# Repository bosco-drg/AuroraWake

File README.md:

# AuroraWake

> A smart alarm clock that gently guides you into waking up instead of startling you.

AuroraWake is a light and sound alarm clock project designed to make waking up feel more natural. The device gradually adjusts its light intensity and, if necessary, adds a gentle sound at the selected time.

## Goals

- Reduce sudden and unpleasant wake-ups.
- Use gradually increasing light as the primary wake-up signal.
- Keep the experience simple, quiet, and respectful of sleep.
- Design an accessible, repairable, and well-documented device.

## Project structure

```text
AuroraWake/
├── docs/        Documentation, schematics, and design decisions
├── hardware/    Schematics, PCB, and manufacturing files
└── README.md    Project overview
```

## Development status

The project is currently in the electronic design phase. The overall architecture is built around an **ESP32** controller, which will coordinate:

- gradual lighting through a voltage dimmer;
- alarm information on the display;
- the speaker through an audio amplifier;
- the physical buttons and the RTC clock;
- Bluetooth communication with a smartphone application.

The next step is to select suitable components and check their compatibility. The schematic will then be refined before the first prototype is designed.

<div align="center">
	
</div>

<p align="center"><em>Preliminary functional architecture of AuroraWake.</em></p>

## Author

Project designed and developed by **Bosco drg**.

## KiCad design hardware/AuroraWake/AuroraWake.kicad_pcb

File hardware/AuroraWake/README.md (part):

# AuroraWake V2 — Carte réveil ESP32-S3 (12 V)

Projet KiCad 9, **schéma complet sur une seule feuille A1** (8 blocs fonctionnels encadrés), généré depuis [tools/design.py](tools/design.py).
ERC : **0 erreur, 1 avertissement accepté** (pad thermique du MAX98357A, de type « unspecified », relié à GND).
Le schéma est exporté en PDF dans [docs/AuroraWake_schema.pdf](docs/AuroraWake_schema.pdf) et la BOM brute KiCad dans [docs/bom_kicad.csv](docs/bom_kicad.csv).

## 0. Décisions et hypothèses

| Sujet | Décision | Pourquoi |
|---|---|---|
| Entrée | Jack DC conservé : **CUI PJ-063AH, 8 A** | Un jack ne supporte pas 17 A, donc le **panneau est limité à 50 W (4,2 A)**. Courant total ≈ 4,9 A, soit environ 60 % du calibre du jack. |
| Panneau 60 W | Possible, avec un fusible NANO² **10 A** | 5,7 A au total : le fusible de 7 A fonctionnerait alors à 81 % de son calibre, au-delà de la règle des 75 %. La marge sur le jack se réduit. |
| Bloc d'alimentation | **12 V ≥ 6 A** (≥ 8 A pour un panneau de 60 W) | — |
| Module | **ESP32-S3-WROOM-1-N16R8** (module nu) | 16 Mo de flash pour les sons, 8 Mo de PSRAM pour les tampons audio. Un DevKitC-1 N16R8 suffit pour développer le firmware en attendant les cartes. |
| Fabrication | JLCPCB PCBA, **2 couches, cuivre 2 oz**, environ 100 × 80 mm | Les pièces traversantes (jack, bornier, boutons, buzzer, barrettes) sont soudées à la main ou en option THT. |
| Références LCSC | **Non renseignées** | À compléter au moment du rapprochement de la BOM chez JLCPCB. Chaque MPN est dans le champ `MPN` du symbole. |

## 1. BOM (justifiée)

Liste complète et regroupée : [docs/bom_kicad.csv](docs/bom_kicad.csv), soit 112 composants. Les composants structurants :

| Réf | Composant | Boîtier | Justification / alternative |
|---|---|---|---|
| J101 | Jack DC CUI PJ-063AH | THT | Jack 8 A. Broche centrale de 2,0 mm : **vérifier la fiche du bloc d'alimentation** (5,5×2,1). |
| F101 | Fusible Littelfuse NANO² 451, **7 A rapide** (0451007.MRL) | CMS 7,5 × 3,8 mm | 10 fois plus petit que le 5×20, assemblé par JLCPCB. Charge de 70 % à 4,9 A. L'appel de courant de C101 au branchement (≈0,3 A²s) reste très inférieur à l'I²t du fusible : à vérifier dans la datasheet. Soudé, donc non remplaçable ; pour un fusible remplaçable, utiliser le porte-fusible OMNI-BLOK 157x, de même encombrement. |
| Q101 | AOD4185 (P-MOS −40 V, ≈15 mΩ) | TO-252 | Protection contre l'inversion de polarité : 0,36 W de pertes contre ≈2,5 W pour une Schottky. Alternative : contrôleur de diode idéale LM74700 avec un N-MOS. |
| D101 | BZT52C15 | SOD-123 | Limite Vgs de Q101 à 15 V (maximum autorisé : ±20 V). |
| D102 | SMBJ15A (TVS 600 W) | SMB | Écrête les surtensions à ~24 V. Placée **après** Q101 pour ne pas être sollicitée en cas d'inversion. |
| C101 / C102 | 470 µF 35 V électrolytique / 10 µF 35 V X7R | 10×10,5 / 1210 | Réservoir pour les fronts PWM. L'électrolytique amortit le pic de branchement à chaud (risque élevé avec des céramiques seules). |
| NT101 | Net-tie 2 mm | SMD | **Seul** point de liaison PGND ↔ GND. |
| U101 | AP63205WU (buck 5 V / 2 A, Vin 3,8–32 V) | TSOT-23-6 | Sortie fixe 5 V, peu de composants, supporte 32 V (au-dessus de l'écrêtage TVS). Alternative : TPS563201, limité à 17 V, rejeté. |
| L101 | 4,7 µH, Isat ≥ 3,5 A (Bourns SRN6045TA) | 6×6 mm | Ondulation d'environ 0,56 A crête à crête à 1,1 MHz, soit 28 % de 2 A. |
| R102 / R103 | 100k / 15k sur EN | 0603 | Seuil de démarrage (UVLO) à ~9 V : pas de fonctionnement sur un bloc qui s'effondre. |
| D103 / D104 | SS34 | SMA | OU de diodes 5 V ↔ VBUS : la logique est alimentée par l'USB seul pour flasher. Alternative : un P-MOS en diode idéale pour gagner 0,4 V. |
| U102 | AP7361C-33E (LDO 1 A, chute 0,36 V) | SOT-223 | **Remplace l'AMS1117** : avec VSYS ≈ 4,55 V (après Schottky), la chute de 1,1–1,3 V de l'AMS1117 est trop juste. Stable avec céramiques. |
| U201 | ESP32-S3-WROOM-1-N16R8 | Module | Wi-Fi + BLE, USB natif, I2S, assez de GPIO. |
| U202 | USBLC6-2SC6 | SOT-23-6 | Protection ESD sur D+, D− et VBUS. |
| J201 | USB-C HRO TYPE-C-31-M-12 | SMD | Programmation et débogage via l'USB-Serial-JTAG intégré. CC1/CC2 tirées à GND par 5,1 kΩ. |
| J202 / J203 | Barrettes 1×6 UART / 1×8 extension+JTAG | 2,54 mm | Secours pour la programmation, sonde ESP-Prog. |
| Q301 | AOD4184A (N-MOS 40 V, ≈9 mΩ @ 4,5 V) | TO-252 | 0,2 W dissipés à 4,2 A. **L'IRLZ44N de la simulation SPICE n'est pas garanti à Vgs = 3,3 V.** |
| U301 | UCC27511A (driver de grille 4 A) | SOT-23-6 | Sorties OUTH/OUTL séparées (Ron 10 Ω / Roff 4,7 Ω). Alimenté en 5 V, donc Vgs reste toujours sous 20 V. Entrées compatibles 3,3 V. |
| D301 | SS54 (5 A 40 V) | SMC | Roue libre sur l'inductance du câble du panneau. |
| J301 | Bornier 5,08 mm 2 points (≥ 15 A) | THT | Raccordement du panneau. |
| U401 | MAX98357AETE+T | TQFN-16 3×3 | Classe D I2S, 3,2 W / 4 Ω, pas de DAC externe. |
| FB401–403 | Ferrites 0805, 2 A | 0805 | Isolent le 5 V audio et filtrent la CEM sur les fils du haut-parleur. |
| BZ401 / Q401 | Buzzer passif 12 mm + AO3400A + 1N4148W | THT / SOT-23 | Alarme de secours si la carte SD est absente. |
| J501 | microSD Hirose DM3AT avec détection de carte | SMD | Push-push, avec détection. |
| U501 | TPD4E05U06 | USON-10 | ESD sur CLK, CMD, DAT0 et DAT3. **Pas de translateur de niveau** : la carte SD est en 3,3 V, comme l'ESP32. |
| U601 | DS3231SN# | SOIC-16W | TCXO ±2 ppm (DS3231M : ±5 ppm). Les broches NC 5–12 sont reliées à GND. |
| BT601 | Porte-pile CR2032 Keystone 3034 | SMD | Autonomie > 5 ans. |
| J701 | Barrette femelle 1×4 pour module OLED SSD1306 0,96" 128×64, I2C 0x3C | THT | **Vérifier l'ordre GND/VCC du module acheté.** |
| SW801–803 | Boutons 6×6 mm, H8 | THT | Antirebond RC 10k/100 nF (τ = 1 ms) et 1k en série. |

## 2. Architecture et budgets

```mermaid
flowchart LR
  JACK[Jack 12 V 8 A] --> F[F101 7 A] --> RP[Q101 anti-inversion<br/>+ TVS SMBJ15A] --> V12((+12V))
  V12 --> LED[J301 panneau LED ≤50 W] --> Q[Q301 N-MOS<br/>UCC27511A] --> PGND((PGND))
  V12 --> BUCK[U101 AP63205<br/>buck 5 V 2 A] --> V5((+5V))
  V5 --> AMP[U401 MAX98357A] --> HP[HP 4 Ω 3 W]
  V5 --> BUZ[Buzzer]
  V5 --> DRV[Driver de grille]
  V5 -->|SS34| VSYS((VSYS))
  USB[USB-C] -->|VBUS / SS34| VSYS
  VSYS --> LDO[U102 AP7361C] --> V33((+3V3))
  V33 --> ESP[ESP32-S3]
  V33 --> SD[microSD]
  V33 --> RTC[DS3231 + CR2032]
  V33 --> OLED[OLED SSD1306]
  ESP -- PWM --> DRV
  ESP -- I2S --> AMP
  ESP -- SPI --> SD
  ESP -- I2C --> RTC & OLED
  BTN[3 boutons] --> ESP
  PGND --- NT[NT101 point unique] --- GND((GND))
```

### Budget de courant

| Rail | Consommateur | Typique | Crête |
|---|---|---:|---:|
| +3V3 | ESP32-S3 (Wi-Fi en émission) | 120 mA | 500 mA |
| | Carte SD (écriture) | 20 mA | 100 mA |
| | OLED, RTC, LED, pull-ups | 20 mA | 31 mA |
| | **Total 3V3** | **≈160 mA** | **≈630 mA** (LDO 1 A, dissipation de 0,2 W typique à 0,8 W en crête) |
| +5V | Ampli (3,2 W / 85 %) | 150 mA (≈0,5 W) | 750 mA |
| | Buzzer, driver de grille | — | 45 mA |
| | VSYS (rail 3V3 en amont du LDO) | 160 mA | 630 mA |
| | **Total 5V** | **≈310 mA** | **≈1,43 A** (buck de 2 A, soit 71 %) |
| +12V | Buck (rendement 88 %) | 0,15 A | 0,68 A |
| | Panneau LED 50 W / 60 W | 0–4,2 A | 4,2 / 5,0 A |
| | **Total à l'entrée** | | **4,84 A** (50 W) / **5,68 A** (60 W) |

Veille la nuit (écran au minimum, Wi-Fi coupé) : environ 20 mA sous 12 V.

Pertes à pleine charge (50 W) : fusible ≈0,5 W, Q101 0,36 W, Q301 0,2 W, contact du jack ≈0,4 W. Il faut 2–4 cm² de cuivre sous chaque TO-252, avec des vias thermiques vers la face inférieure.

### Largeur des pistes (IPC-2221, cuivre externe 2 oz)

| Chemin | Courant | Minimum calculé (ΔT 10 °C) | **Valeur retenue** (classe de net) |
|---|---:|---:|---|
| Jack → F101 → Q101 → +12V → J301 → Q301 → PGND → jack | 5,7 A | 1,66 mm | **≥ 3 mm ou polygones** (`PWR_LED`) |
| +5V, VSYS, +5V_AUD, BUCK_SW, +3V3, sorties HP | ≤ 2 A | 0,39 mm | **1 mm** (`PWR_5V`) |
| Signaux | — | — | 0,25 mm, isolement 0,2 mm (`Default`) |
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
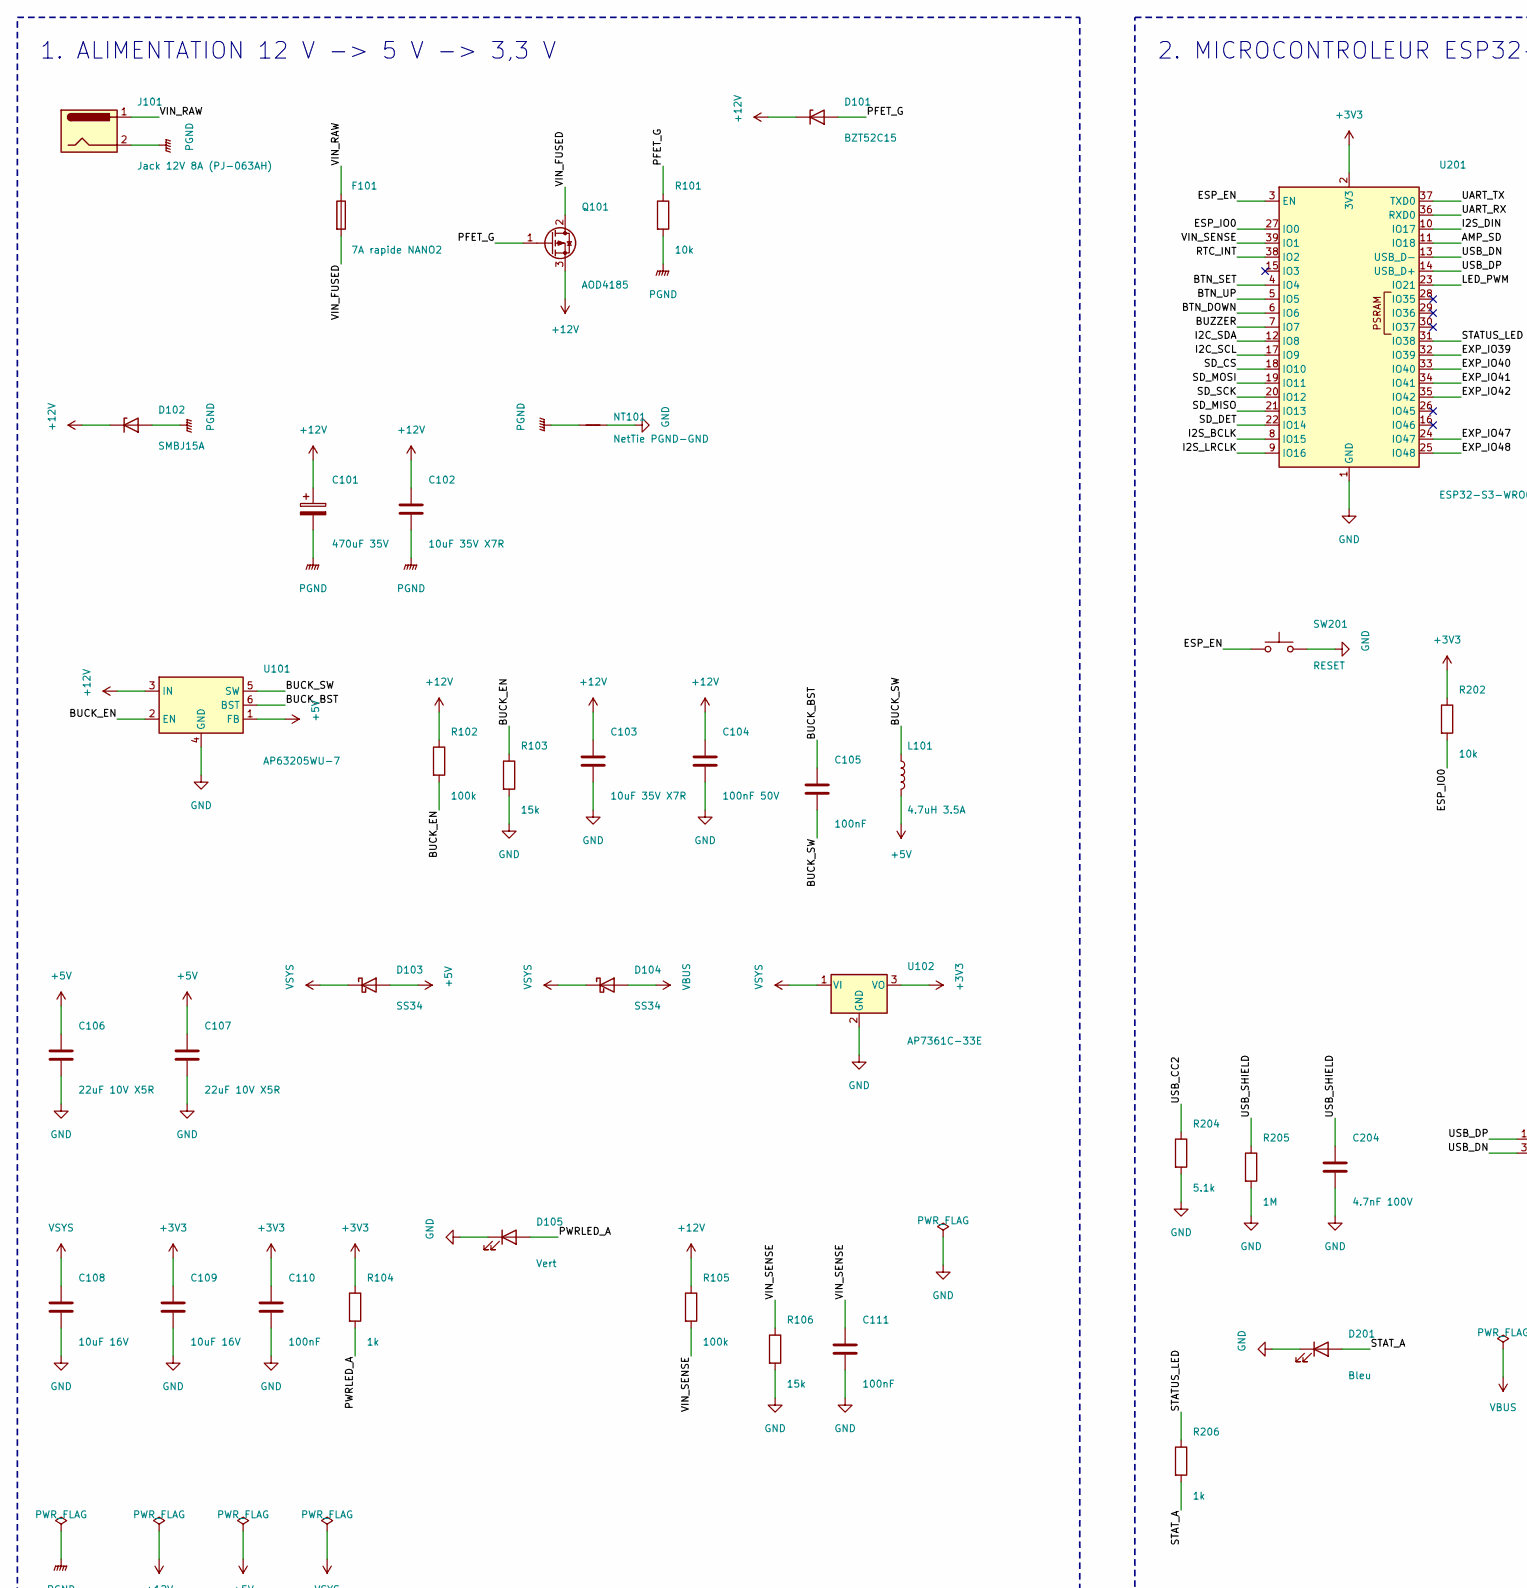
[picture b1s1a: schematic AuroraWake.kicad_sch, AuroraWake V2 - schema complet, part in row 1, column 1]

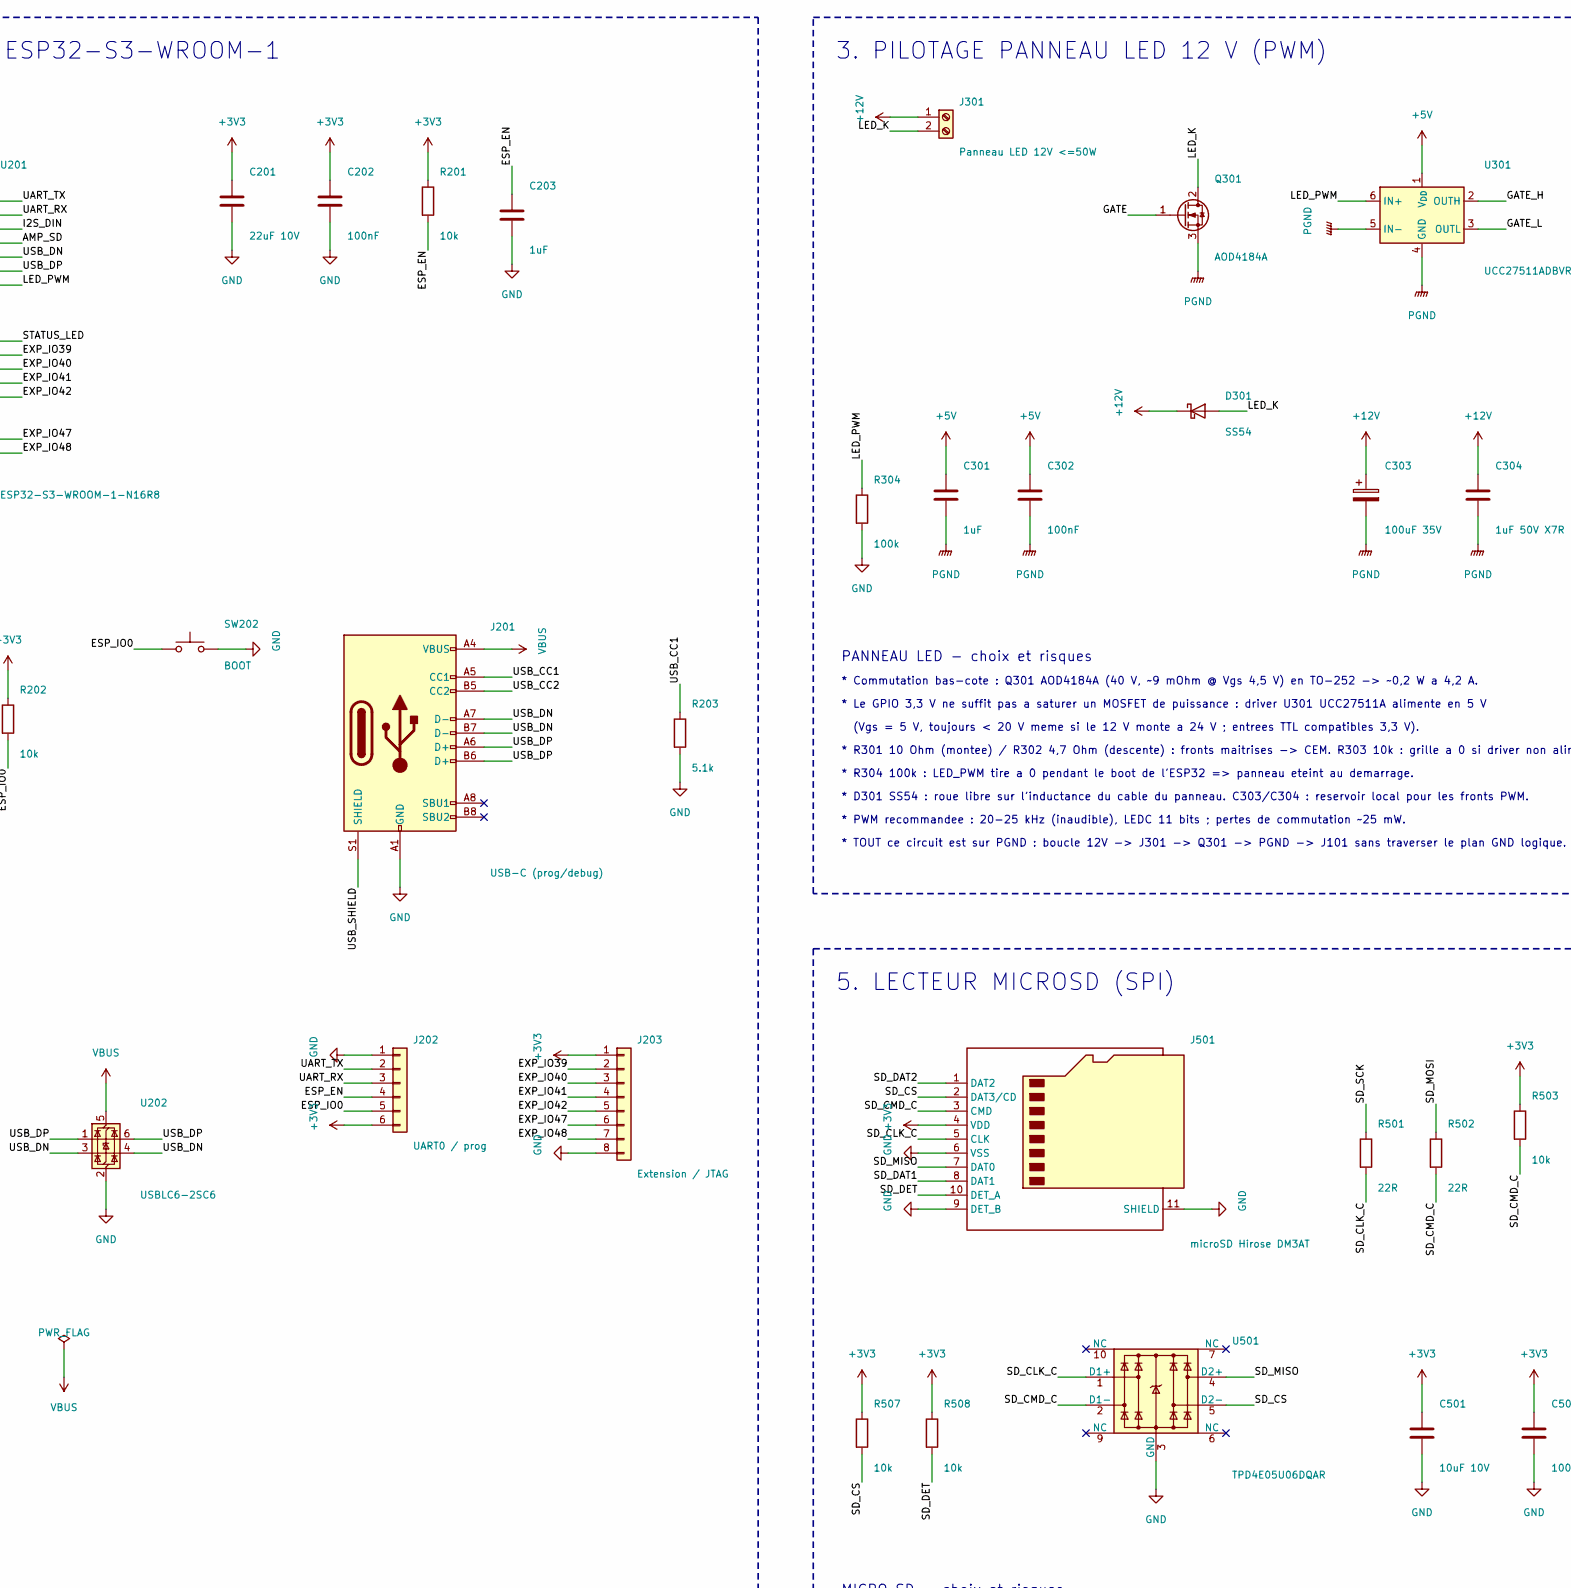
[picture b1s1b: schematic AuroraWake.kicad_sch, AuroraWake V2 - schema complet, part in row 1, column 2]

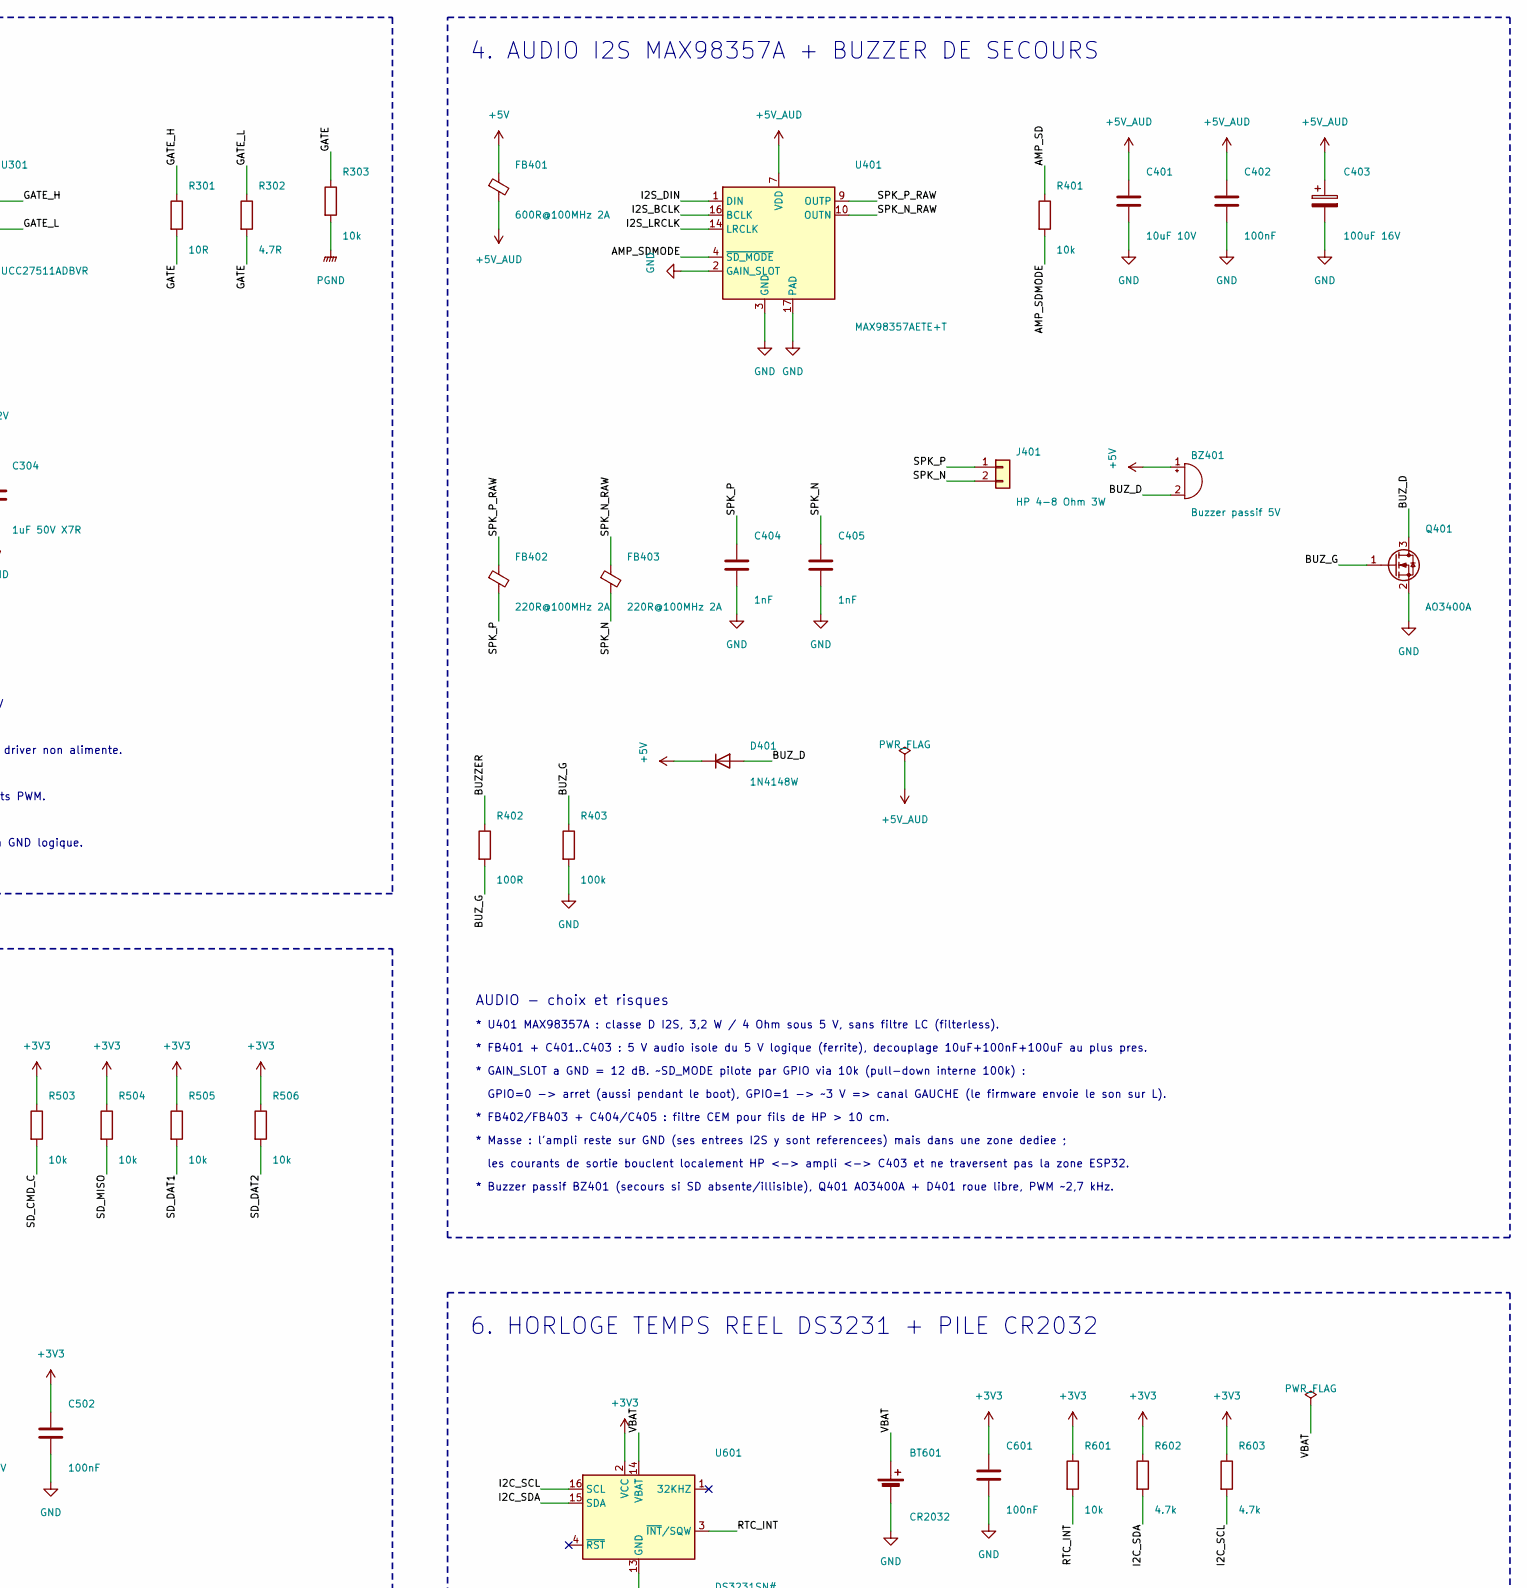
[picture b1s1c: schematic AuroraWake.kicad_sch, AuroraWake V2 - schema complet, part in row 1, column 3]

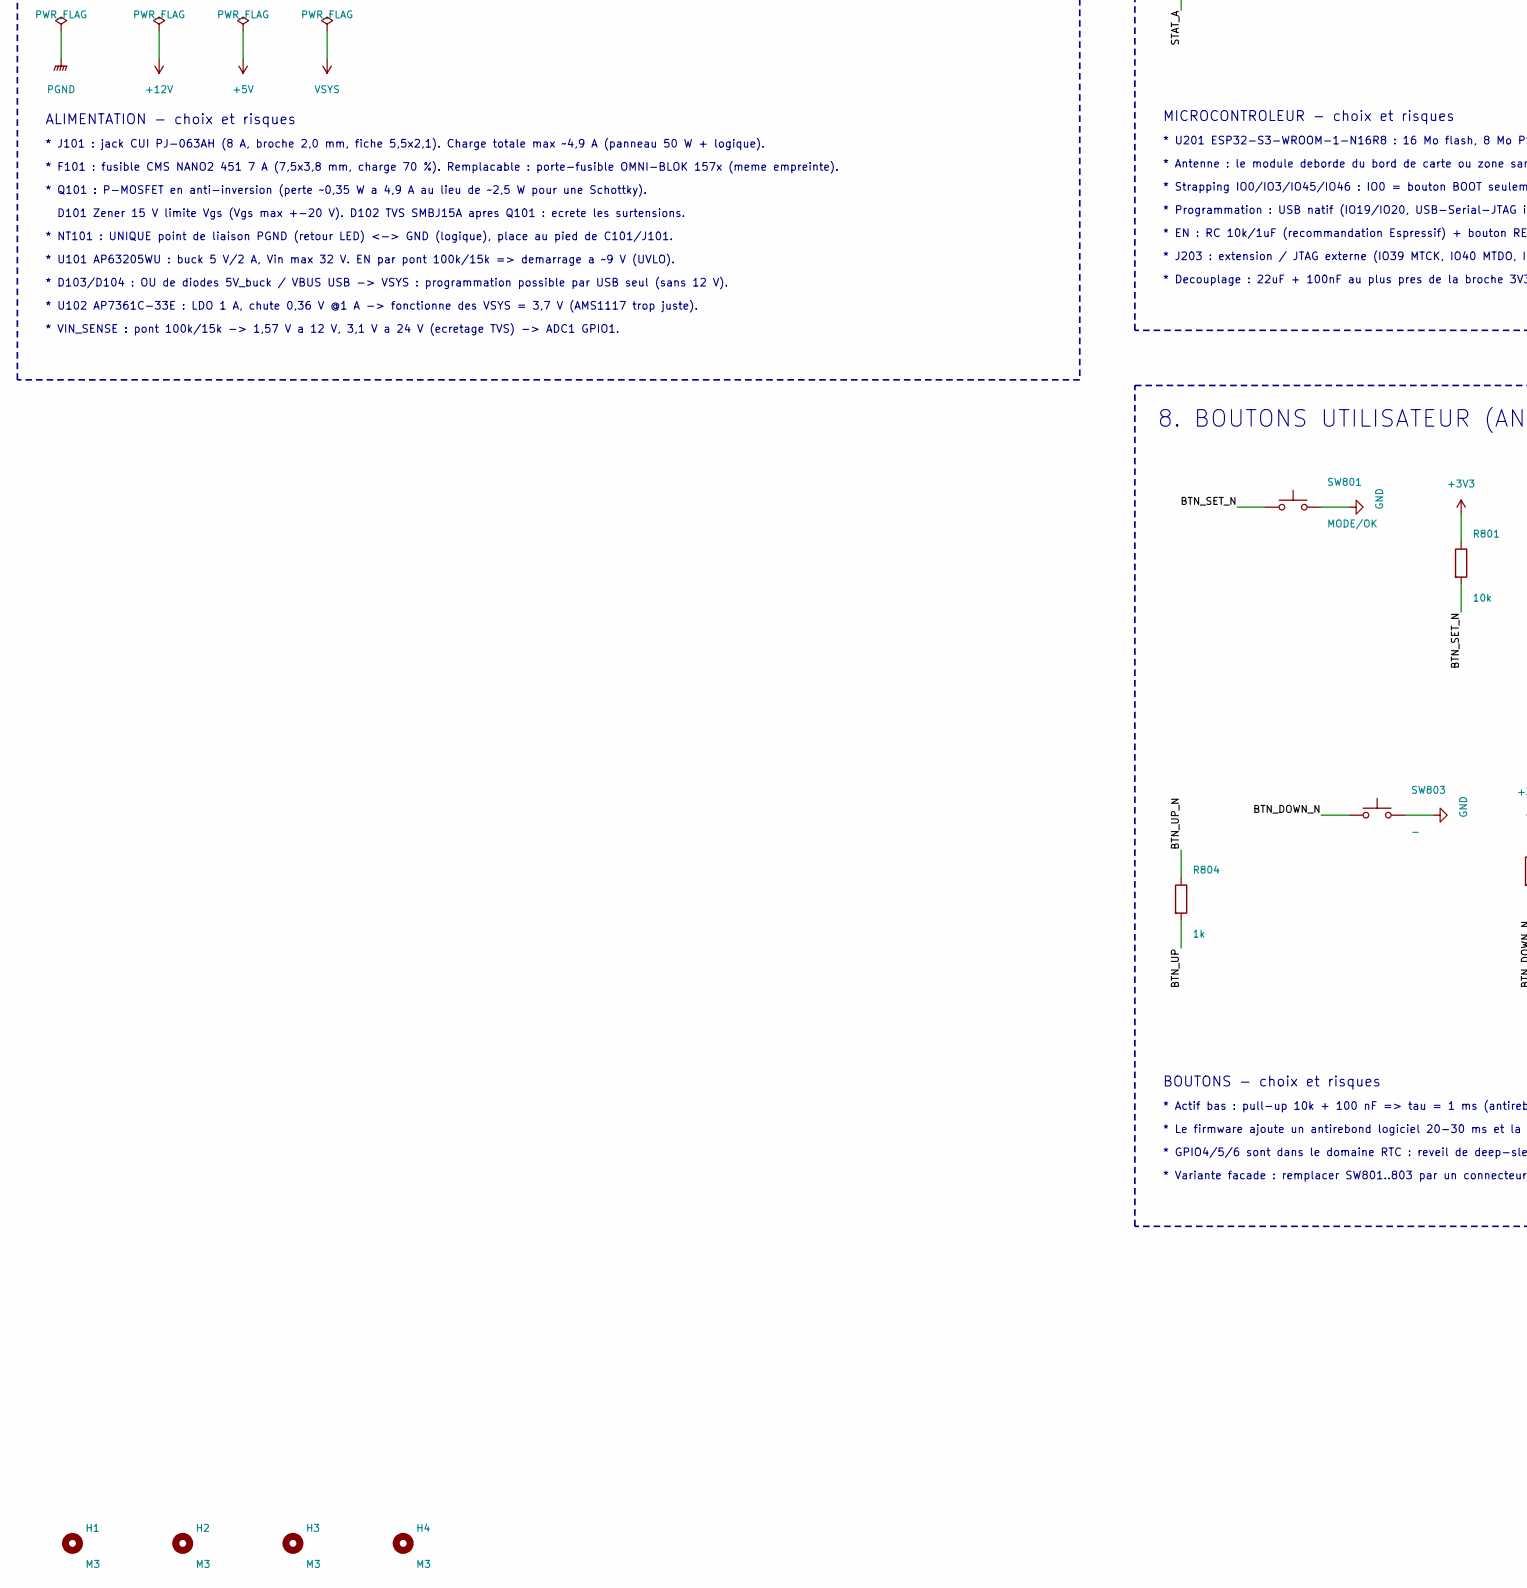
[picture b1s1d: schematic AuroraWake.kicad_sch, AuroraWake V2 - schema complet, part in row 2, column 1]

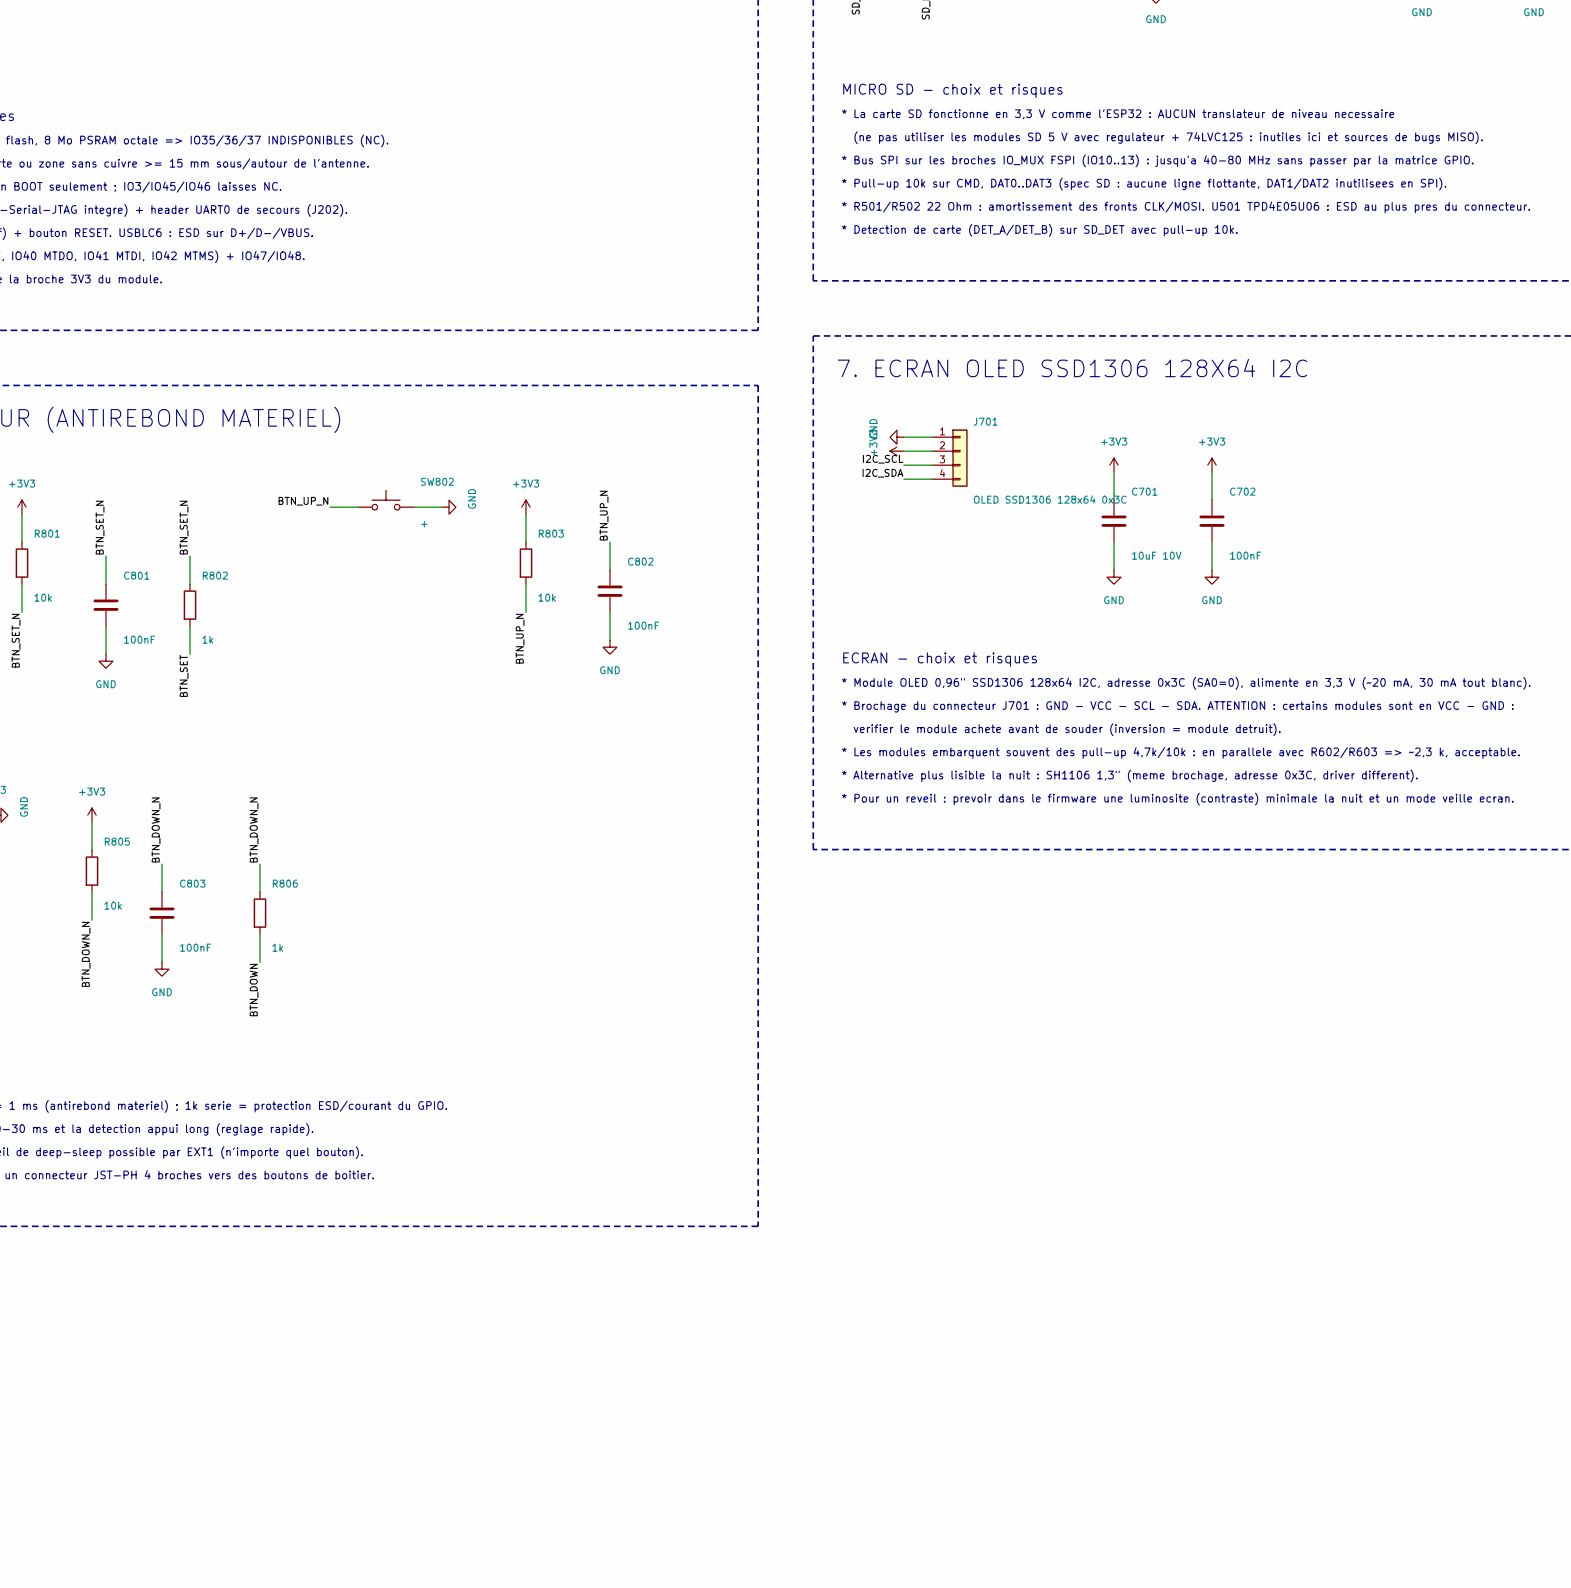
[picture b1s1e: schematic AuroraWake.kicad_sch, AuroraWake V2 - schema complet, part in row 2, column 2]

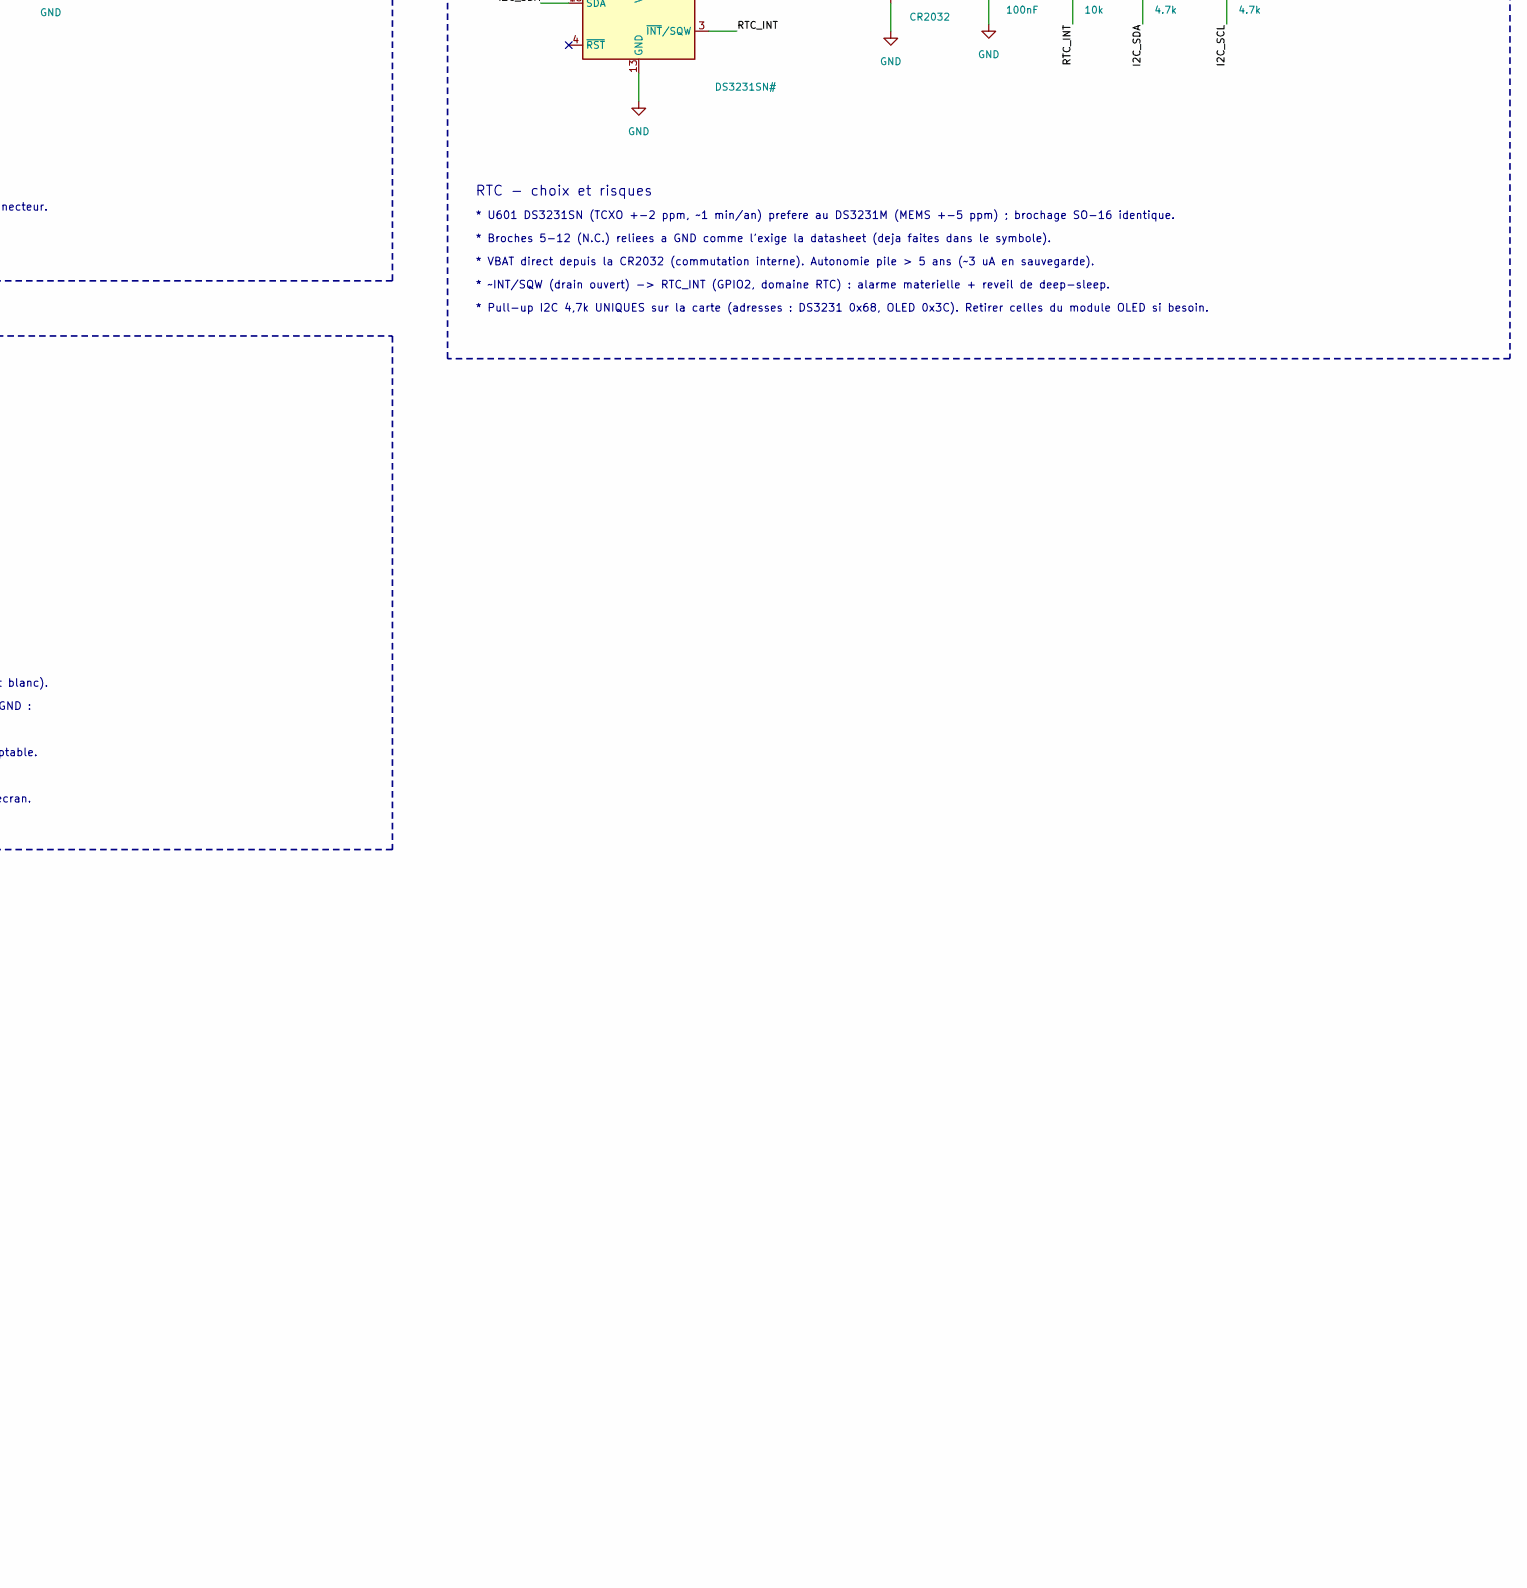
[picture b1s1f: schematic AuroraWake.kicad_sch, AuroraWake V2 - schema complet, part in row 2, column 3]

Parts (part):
BT601: CR2032; BatteryHolder_Keystone_3034_1x20mm; MPN Keystone 3034
BZ401: Buzzer passif 5V; Buzzer_12x9.5RM7.6
C101: 470uF 35V; CP_Elec_10x10.5; LCSC C2992611
C102, C103: 10uF 35V X7R; C_1210_3225Metric; LCSC C5156756
C104: 100nF 50V; C_0603_1608Metric; LCSC C14663
C105, C110, C111, C202, C302, C402, C502, C601, C702, C801, C802, C803: 100nF; C_0603_1608Metric; LCSC C14663
C106, C107: 22uF 10V X5R; C_1206_3216Metric; LCSC C12891
C108, C109: 10uF 16V; C_0805_2012Metric; LCSC C15850
C201: 22uF 10V; C_0805_2012Metric; LCSC C45783
C203, C301: 1uF; C_0603_1608Metric; LCSC C15849
C204: 4.7nF 100V; C_0603_1608Metric; LCSC C115052
C303: 100uF 35V; CP_Elec_8x10.5; LCSC C2992597
C304: 1uF 50V X7R; C_1206_3216Metric; LCSC C1848
C401, C501, C701: 10uF 10V; C_0805_2012Metric; LCSC C15850
C403: 100uF 16V; CP_Elec_6.3x5.4; LCSC C5155334
C404, C405: 1nF; C_0603_1608Metric; LCSC C1588
D101: BZT52C15; D_SOD-123; LCSC C19077412
D102: SMBJ15A; D_SMB; MPN SMBJ15A (TVS unidirectionnelle 600 W); LCSC C2760888
D103, D104: SS34; D_SMA; LCSC C8678
D105: Vert; LED_0603_1608Metric; MPN Hubei KENTO KT-0603G; LCSC C12624
D201: Bleu; LED_0603_1608Metric; MPN Hubei KENTO KT-0603B; LCSC C2288
D301: SS54; D_SMC; MPN SS54 (5 A 40 V); LCSC C22452
D401: 1N4148W; D_SOD-123; LCSC C81598
F101: 7A rapide NANO2; Fuse_Littelfuse-NANO2-451_453; MPN Littelfuse 0451007.MRL (NANO2 451, 7 A,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; LCSC C99548
FB401: 600R@100MHz 2A; L_0805_2012Metric; LCSC C41384117
FB402, FB403: 220R@100MHz 2A; L_0805_2012Metric; MPN Murata BLM21PG221SN1D; LCSC C85840
H1, H2, H3, H4: M3; MountingHole_3.2mm_M3
J101: Jack 12V 8A (PJ-063AH); BarrelJack_CUI_PJ-063AH_Horizontal; MPN CUI PJ-063AH
J201: USB-C (prog/debug); USB_C_Receptacle_HRO_TYPE-C-31-M-12; MPN HRO TYPE-C-31-M-12; LCSC C165948
J202: UART0 / prog; PinHeader_1x06_P2.54mm_Vertical
J203: Extension / JTAG; PinHeader_1x08_P2.54mm_Vertical
J301: Panneau LED 12V <=50W; TerminalBlock_Phoenix_MKDS-3-2-5.08_1x02_P5.08mm_Horizontal; MPN Bornier 5,08 mm >= 15 A
J401: HP 4-8 Ohm 3W; JST_PH_B2B-PH-K_1x02_P2.00mm_Vertical
J501: microSD Hirose DM3AT; microSD_HC_Hirose_DM3AT-SF-PEJM5; MPN Hirose DM3AT-SF-PEJM5; LCSC C114218
J701: OLED SSD1306 128x64 0x3C; PinSocket_1x04_P2.54mm_Vertical
L101: 4.7uH 3.5A; L_Bourns_SRN6045TA; MPN Bourns SRN6045TA-4R7M (Isat >= 3,5 A); LCSC C2044594
NT101: NetTie PGND-GND; NetTie-2_SMD_Pad2.0mm
Q101: AOD4185; TO-252-2; MPN AOD4185 (P-MOS -40V -40A, ~15mOhm); LCSC C5371006
Q301: AOD4184A; TO-252-2; MPN AOD4184A (N-MOS 40V 50A); LCSC C99124
Q401: AO3400A; SOT-23; LCSC C20917
R101, R201, R202, R303, R401, R503, R504, R505, R506, R507, R508, R601, R801, R803, R805: 10k; R_0603_1608Metric; LCSC C25804
R102, R105, R304, R403: 100k; R_0603_1608Metric; LCSC C25803
R103, R106: 15k; R_0603_1608Metric; LCSC C22809
R104, R206, R802, R804, R806: 1k; R_0603_1608Metric; LCSC C21190
R203, R204: 5.1k; R_0603_1608Metric; LCSC C23186
R205: 1M; R_0603_1608Metric; LCSC C22935
R301: 10R; R_0603_1608Metric; LCSC C22859
R302: 4.7R; R_0603_1608Metric; LCSC C23164
R402: 100R; R_0603_1608Metric; LCSC C22775
R501, R502: 22R; R_0603_1608Metric; LCSC C23345
R602, R603: 4.7k; R_0603_1608Metric; LCSC C23162
SW201: RESET; SW_SPST_PTS645Sx43SMTR92; MPN C&K PTS645SM43SMTR92 LFS; LCSC C221880
SW202: BOOT; SW_SPST_PTS645Sx43SMTR92; MPN C&K PTS645SM43SMTR92 LFS; LCSC C221880
SW801: MODE/OK; SW_PUSH_6mm_H8mm
SW802: +; SW_PUSH_6mm_H8mm
SW803: -; SW_PUSH_6mm_H8mm
U101: AP63205WU-7; TSOT-23-6; MPN Diodes AP63205WU-7; LCSC C2071056
U102: AP7361C-33E; SOT-223-3_TabPin2; MPN Diodes AP7361C-33E-13; LCSC C500795
U201: ESP32-S3-WROOM-1-N16R8; ESP32-S3-WROOM-1; MPN Espressif ESP32-S3-WROOM-1-N16R8; LCSC C2913202
U202: USBLC6-2SC6; SOT-23-6; LCSC C2827654
U301: UCC27511ADBVR; SOT-23-6; MPN TI UCC27511ADBVR; LCSC C2676982
U401: MAX98357AETE+T; TQFN-16-1EP_3x3mm_P0.5mm_EP1.23x1.23mm; MPN Analog Devices MAX98357AETE+T; LCSC C910544
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
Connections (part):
+3V3: C109.1, C110.1, C201.1, C202.1, C501.1, C502.1, C601.1, C701.1, C702.1, J202.6, J203.1, J501.4 (VDD), J701.2, R104.1, R201.1, R202.1, R503.1, R504.1, R505.1, R506.1, R507.1, R508.1, R601.1, R602.1, R603.1, R801.1, R803.1, R805.1, U102.3 (VO), U201.2 (3V3), U601.2 (VCC)
+5V: BZ401.1 (+), C106.1, C107.1, C301.1, C302.1, D103.2 (A), D401.1 (K), FB401.1, L101.2, U101.1 (FB), U301.1 (V_{DD})
+5V_AUD: C401.1, C402.1, C403.1, FB401.2, U401.7 (VDD), U401.8 (VDD)
+12V: C101.1, C102.1, C103.1, C104.1, C303.1, C304.1, D101.1 (K), D102.1 (K), D301.1 (K), J301.1, Q101.3 (S), R102.1, R105.1, U101.3 (IN)
/AMP_SD: R401.1, U201.11 (IO18)
/AMP_SDMODE: R401.2, U401.4 (~SD_MODE)
/BTN_DOWN: R806.2, U201.6 (IO6)
/BTN_DOWN_N: C803.1, R805.2, R806.1, SW803.1
/BTN_SET: R802.2, U201.4 (IO4)
/BTN_SET_N: C801.1, R801.2, R802.1, SW801.1
/BTN_UP: R804.2, U201.5 (IO5)
/BTN_UP_N: C802.1, R803.2, R804.1, SW802.1
/BUCK_BST: C105.1, U101.6 (BST)
/BUCK_EN: R102.2, R103.1, U101.2 (EN)
/BUCK_SW: C105.2, L101.1, U101.5 (SW)
/BUZZER: R402.1, U201.7 (IO7)
/BUZ_D: BZ401.2 (-), D401.2 (A), Q401.3 (D)
/BUZ_G: Q401.1 (G), R402.2, R403.1
/ESP_EN: C203.1, J202.4, R201.2, SW201.1, U201.3 (EN)
/ESP_IO0: J202.5, R202.2, SW202.1, U201.27 (IO0)
/EXP_IO39: J203.2, U201.32 (IO39)
/EXP_IO40: J203.3, U201.33 (IO40)
/EXP_IO41: J203.4, U201.34 (IO41)
/EXP_IO42: J203.5, U201.35 (IO42)
/EXP_IO47: J203.6, U201.24 (IO47)
/EXP_IO48: J203.7, U201.25 (IO48)
/GATE: Q301.1 (G), R301.2, R302.2, R303.1
/GATE_H: R301.1, U301.2 (OUTH)
/GATE_L: R302.1, U301.3 (OUTL)
/I2C_SCL: J701.3, R603.2, U201.17 (IO9), U601.16 (SCL)
/I2C_SDA: J701.4, R602.2, U201.12 (IO8), U601.15 (SDA)
/I2S_BCLK: U201.8 (IO15), U401.16 (BCLK)
/I2S_DIN: U201.10 (IO17), U401.1 (DIN)
/I2S_LRCLK: U201.9 (IO16), U401.14 (LRCLK)
/LED_K: D301.2 (A), J301.2, Q301.2 (D)
/LED_PWM: R304.1, U201.23 (IO21), U301.6 (IN+)
/PFET_G: D101.2 (A), Q101.1 (G), R101.1
/PWRLED_A: D105.2 (A), R104.2
/RTC_INT: R601.2, U201.38 (IO2), U601.3 (~INT/SQW)
/SD_CLK_C: J501.5 (CLK), R501.2, U501.1 (D1+)
/SD_CMD_C: J501.3 (CMD), R502.2, R503.2, U501.2 (D1-)
/SD_CS: J501.2 (DAT3/CD), R507.2, U201.18 (IO10), U501.5 (D2-)
/SD_DAT1: J501.8 (DAT1), R505.2
/SD_DAT2: J501.1 (DAT2), R506.2
/SD_DET: J501.10 (DET_A), R508.2, U201.22 (IO14)
/SD_MISO: J501.7 (DAT0), R504.2, U201.21 (IO13), U501.4 (D2+)
/SD_MOSI: R502.1, U201.19 (IO11)
/SD_SCK: R501.1, U201.20 (IO12)
/SPK_N: C405.1, FB403.2, J401.2
/SPK_N_RAW: FB403.1, U401.10 (OUTN)
/SPK_P: C404.1, FB402.2, J401.1
/SPK_P_RAW: FB402.1, U401.9 (OUTP)
/STATUS_LED: R206.1, U201.31 (IO38)
/STAT_A: D201.2 (A), R206.2
/UART_RX: J202.3, U201.36 (RXD0)
/UART_TX: J202.2, U201.37 (TXD0)
/USB_CC1: J201.A5 (CC1), R203.1
/USB_CC2: J201.B5 (CC2), R204.1
/USB_DN: J201.A7 (D-), J201.B7 (D-), U201.13 (USB_D-), U202.3 (I/O2), U202.4 (I/O2)
/USB_DP: J201.A6 (D+), J201.B6 (D+), U201.14 (USB_D+), U202.1 (I/O1), U202.6 (I/O1)
/USB_SHIELD: C204.1, J201.S1 (SHIELD), R205.1
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
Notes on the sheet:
1. ALIMENTATION 12 V -> 5 V -> 3,3 V
ALIMENTATION - choix et risques
* J101 : jack CUI PJ-063AH (8 A, broche 2,0 mm, fiche 5,5x2,1). Charge totale max ~4,9 A (panneau 50 W + logique).
* F101 : fusible CMS NANO2 451 7 A (7,5x3,8 mm, charge 70 %). Remplacable : porte-fusible OMNI-BLOK 157x (meme empreinte).
* Q101 : P-MOSFET en anti-inversion (perte ~0,35 W a 4,9 A au lieu de ~2,5 W pour une Schottky).
D101 Zener 15 V limite Vgs (Vgs max +-20 V). D102 TVS SMBJ15A apres Q101 : ecrete les surtensions.
* NT101 : UNIQUE point de liaison PGND (retour LED) <-> GND (logique), place au pied de C101/J101.
* U101 AP63205WU : buck 5 V/2 A, Vin max 32 V. EN par pont 100k/15k => demarrage a ~9 V (UVLO).
* D103/D104 : OU de diodes 5V_buck / VBUS USB -> VSYS : programmation possible par USB seul (sans 12 V).
* U102 AP7361C-33E : LDO 1 A, chute 0,36 V @1 A -> fonctionne des VSYS = 3,7 V (AMS1117 trop juste).
* VIN_SENSE : pont 100k/15k -> 1,57 V a 12 V, 3,1 V a 24 V (ecretage TVS) -> ADC1 GPIO1.
2. MICROCONTROLEUR ESP32-S3-WROOM-1
MICROCONTROLEUR - choix et risques
* U201 ESP32-S3-WROOM-1-N16R8 : 16 Mo flash, 8 Mo PSRAM octale => IO35/36/37 INDISPONIBLES (NC).
* Antenne : le module deborde du bord de carte ou zone sans cuivre >= 15 mm sous/autour de l'antenne.
* Strapping IO0/IO3/IO45/IO46 : IO0 = bouton BOOT seulement ; IO3/IO45/IO46 laisses NC.
* Programmation : USB natif (IO19/IO20, USB-Serial-JTAG integre) + header UART0 de secours (J202).
* EN : RC 10k/1uF (recommandation Espressif) + bouton RESET. USBLC6 : ESD sur D+/D-/VBUS.
* J203 : extension / JTAG externe (IO39 MTCK, IO40 MTDO, IO41 MTDI, IO42 MTMS) + IO47/IO48.
* Decouplage : 22uF + 100nF au plus pres de la broche 3V3 du module.
3. PILOTAGE PANNEAU LED 12 V (PWM)
PANNEAU LED - choix et risques
* Commutation bas-cote : Q301 AOD4184A (40 V, ~9 mOhm @ Vgs 4,5 V) en TO-252 -> ~0,2 W a 4,2 A.
* Le GPIO 3,3 V ne suffit pas a saturer un MOSFET de puissance : driver U301 UCC27511A alimente en 5 V
(Vgs = 5 V, toujours < 20 V meme si le 12 V monte a 24 V ; entrees TTL compatibles 3,3 V).
* R301 10 Ohm (montee) / R302 4,7 Ohm (descente) : fronts maitrises -> CEM. R303 10k : grille a 0 si driver non alimente.
* R304 100k : LED_PWM tire a 0 pendant le boot de l'ESP32 => panneau eteint au demarrage.
* D301 SS54 : roue libre sur l'inductance du cable du panneau. C303/C304 : reservoir local pour les fronts PWM.
* PWM recommandee : 20-25 kHz (inaudible), LEDC 11 bits ; pertes de commutation ~25 mW.
* TOUT ce circuit est sur PGND : boucle 12V -> J301 -> Q301 -> PGND -> J101 sans traverser le plan GND logique.
4. AUDIO I2S MAX98357A + BUZZER DE SECOURS
AUDIO - choix et risques
* U401 MAX98357A : classe D I2S, 3,2 W / 4 Ohm sous 5 V, sans filtre LC (filterless).
* FB401 + C401..C403 : 5 V audio isole du 5 V logique (ferrite), decouplage 10uF+100nF+100uF au plus pres.
* GAIN_SLOT a GND = 12 dB. ~SD_MODE pilote par GPIO via 10k (pull-down interne 100k) :
GPIO=0 -> arret (aussi pendant le boot), GPIO=1 -> ~3 V => canal GAUCHE (le firmware envoie le son sur L).
* FB402/FB403 + C404/C405 : filtre CEM pour fils de HP > 10 cm.
* Masse : l'ampli reste sur GND (ses entrees I2S y sont referencees) mais dans une zone dediee ;
les courants de sortie bouclent localement HP <-> ampli <-> C403 et ne traversent pas la zone ESP32.
* Buzzer passif BZ401 (secours si SD absente/illisible), Q401 AO3400A + D401 roue libre, PWM ~2,7 kHz.
